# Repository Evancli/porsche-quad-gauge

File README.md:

# QUAD GAUGE FOR A PORSCHE 914
More info [here](https://evanli.com/quad-gauge-for-a-porsche-914/).

## Required Items
This gauge uses salvaged components from a Porsche 944 fuel gauge; the bezel, glass, and face plate. You can used the vintage gauges from the 944 or the corresponding gauges from your 914. It also required two new VDO gauges for voltage and oil pressure.

## Disassembly Tips
It's quite laborious to open these VDO gauges, even with the right tools. A prying spudger and flat implement are needed. Lots of care and attention to not mess up the sheet metal. Be very careful when you pry open the 944 fuel gauge. It's very easy damage the surface finish of the bezel. 

## Processes
The build uses 3D printed parts as well a laser cut and etched parts. 

## License
Shield: [![CC BY-SA 4.0][cc-by-sa-shield]][cc-by-sa]

This work is licensed under a
[Creative Commons Attribution-ShareAlike 4.0 International License][cc-by-sa].

[![CC BY-SA 4.0][cc-by-sa-image]][cc-by-sa]

[cc-by-sa]: http://creativecommons.org/licenses/by-sa/4.0/
[cc-by-sa-image]: https://licensebuttons.net/l/by-sa/4.0/88x31.png
[cc-by-sa-shield]: https://img.shields.io/badge/License-CC%20BY--SA%204.0-lightgrey.svg

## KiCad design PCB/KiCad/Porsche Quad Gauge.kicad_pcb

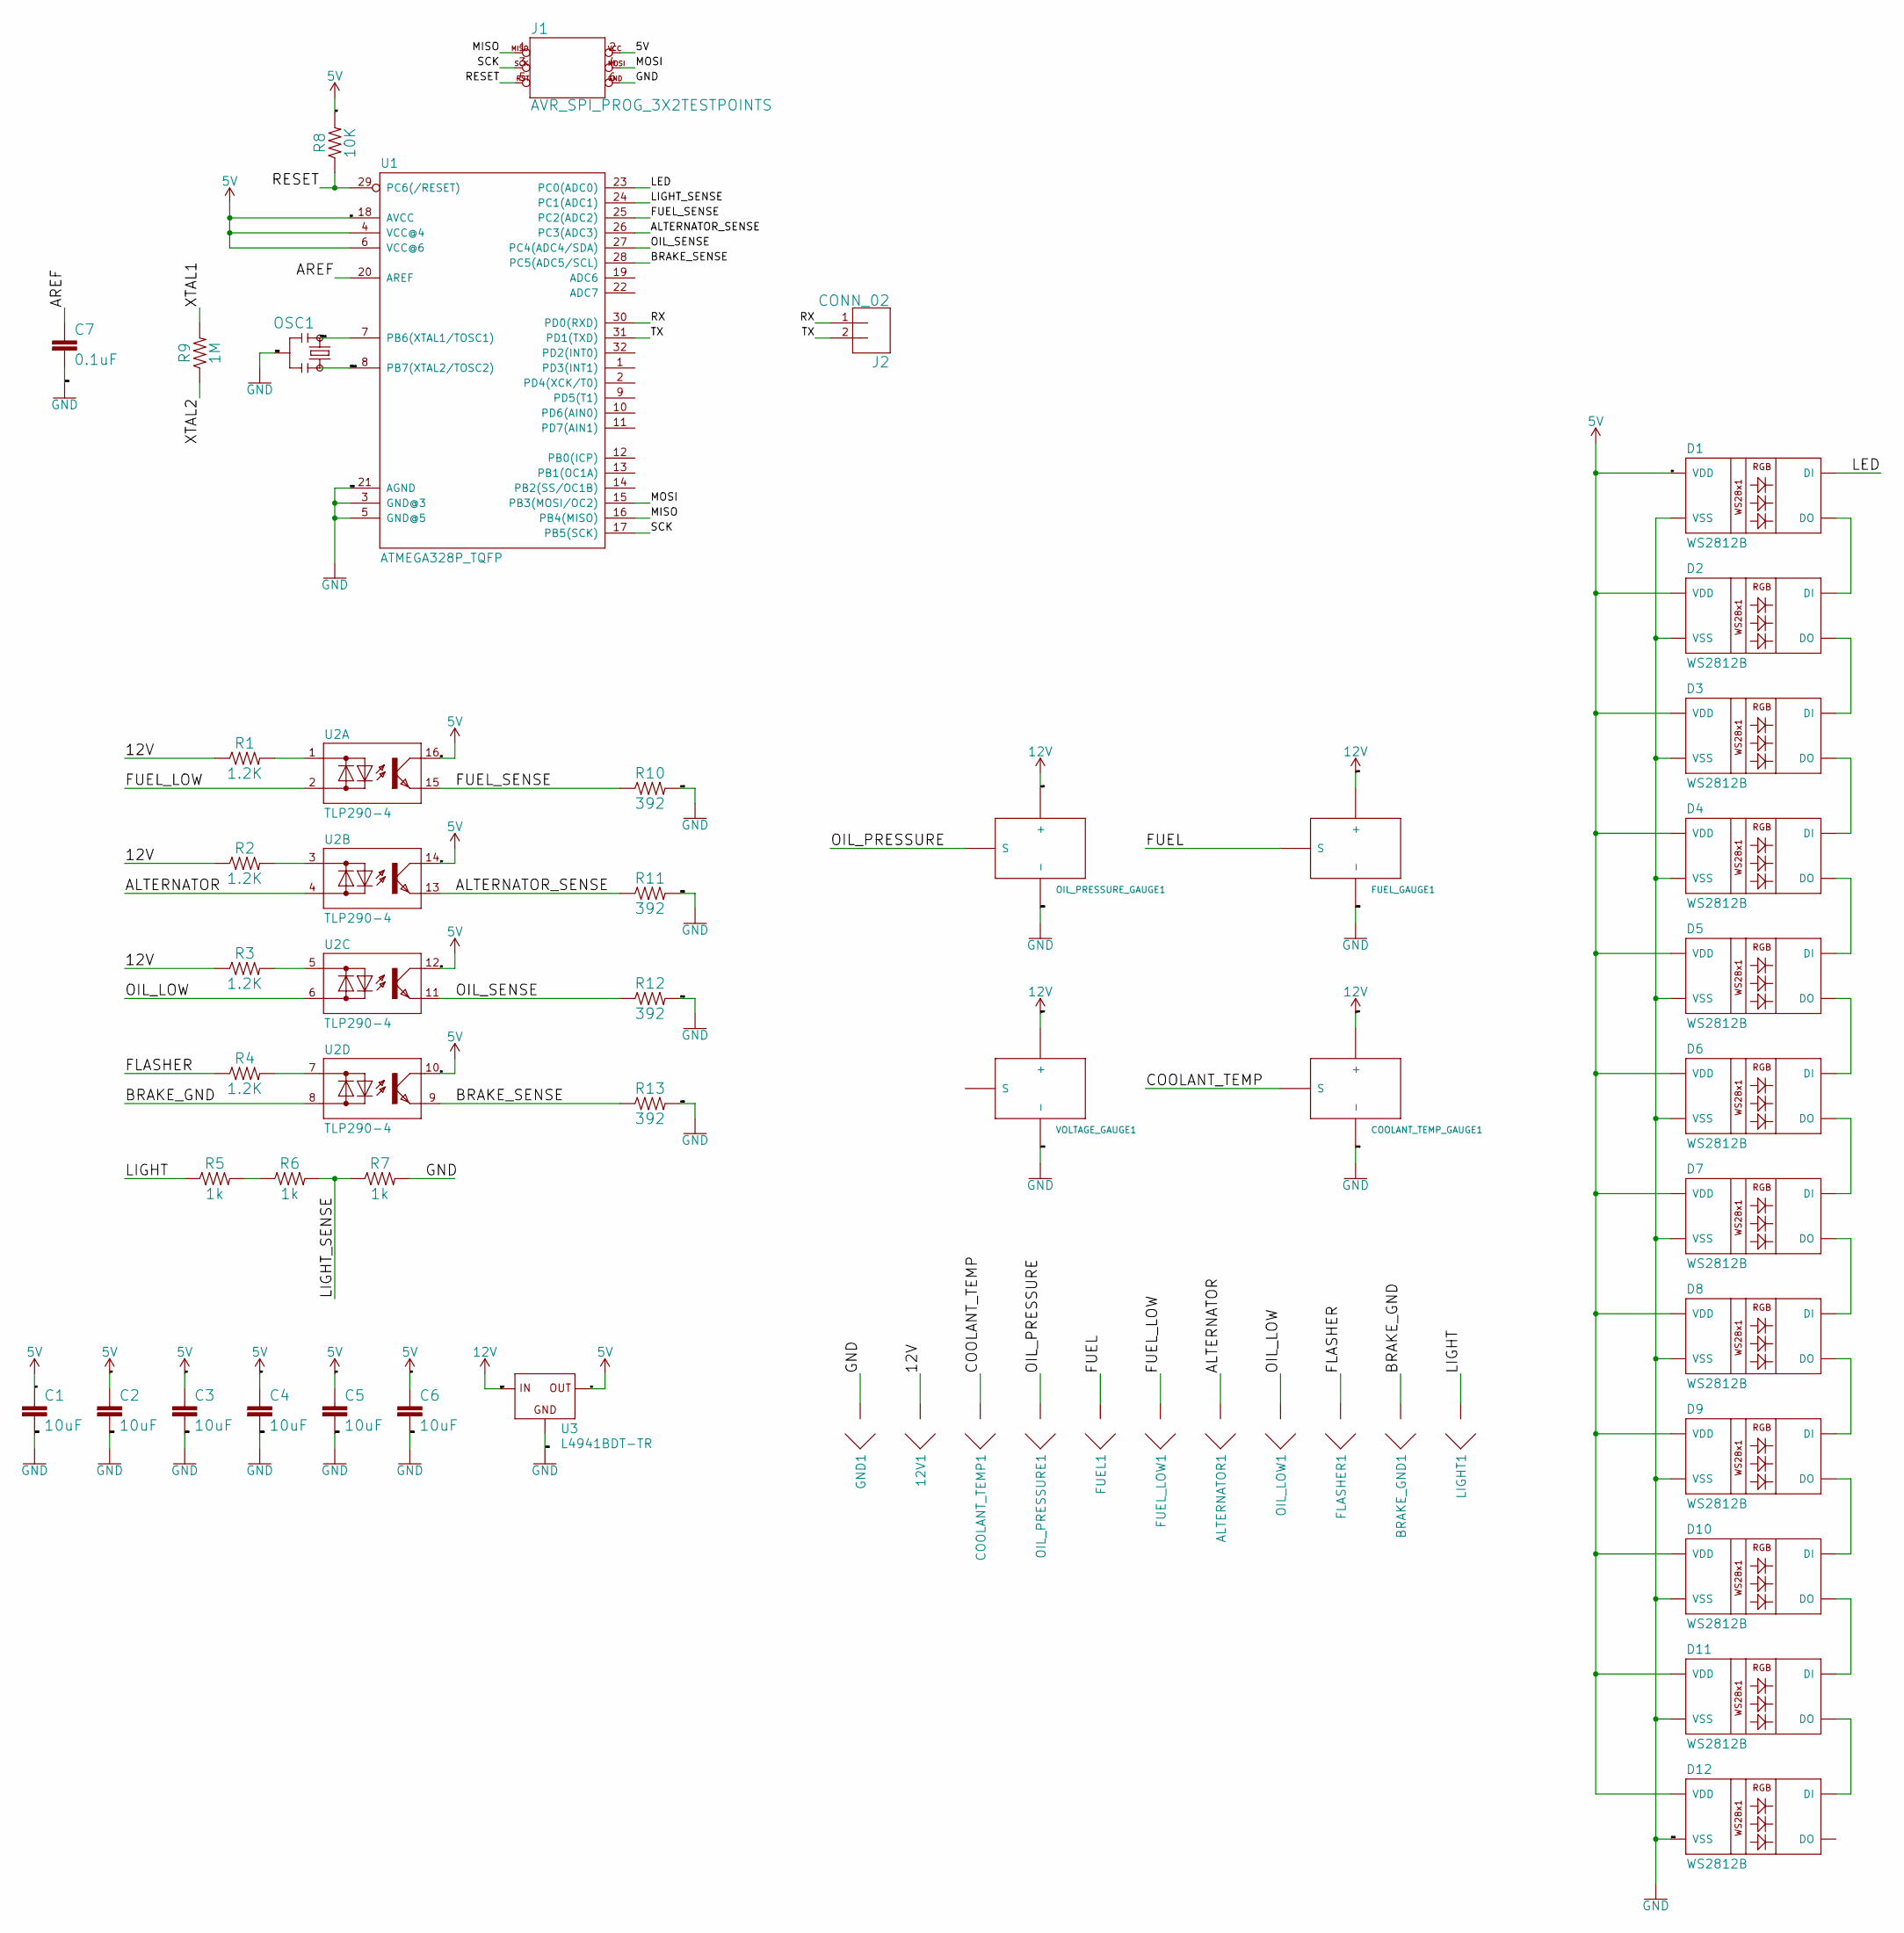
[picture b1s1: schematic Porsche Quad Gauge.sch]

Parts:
12V1: CONNECTOR_QC_TAB_0.25; CONNECTOR_QC_TAB-0.25
ALTERNATOR1: CONNECTOR_QC_TAB_0.25; CONNECTOR_QC_TAB-0.25
BRAKE_GND1: CONNECTOR_QC_TAB_0.25; CONNECTOR_QC_TAB-0.25
C1, C2, C3, C4, C5, C6: 10uF; 0805
C7: 0.1uF; 0805
COOLANT_TEMP1: CONNECTOR_QC_TAB_0.25; CONNECTOR_QC_TAB-0.25
COOLANT_TEMP_GAUGE1: VDO_OLD; VDO_GAUGE_SOCKET
D1, D2, D3, D4, D5, D6, D7, D8, D9, D10, D11, D12: WS2812B
FLASHER1: CONNECTOR_QC_TAB_0.25; CONNECTOR_QC_TAB-0.25
FUEL1: CONNECTOR_QC_TAB_0.25; CONNECTOR_QC_TAB-0.25
FUEL_GAUGE1: VDO_OLD; VDO_GAUGE_SOCKET
FUEL_LOW1: CONNECTOR_QC_TAB_0.25; CONNECTOR_QC_TAB-0.25
GND1: CONNECTOR_QC_TAB_0.25; CONNECTOR_QC_TAB-0.25
J1: AVR_SPI_PROG_3X2TESTPOINTS; 2X3_TEST_POINTS
J2: CONN_02; 1X02
LIGHT1: CONNECTOR_QC_TAB_0.25; CONNECTOR_QC_TAB-0.25
OIL_LOW1: CONNECTOR_QC_TAB_0.25; CONNECTOR_QC_TAB-0.25
OIL_PRESSURE1: CONNECTOR_QC_TAB_0.25; CONNECTOR_QC_TAB-0.25
OIL_PRESSURE_GAUGE1: VDO_NEW; VDO_NEW_GAUGE_SOCKET
OSC1: PRQC16.00SR1010V00L; 3-SMD
R1, R2, R3, R4: 1.2K; 0805
R5, R6, R7: 1k; 0805
R8: 10K; 0805
R9: 1M; 0805
R10, R11, R12, R13: 392; 0805
U1: ATMEGA328P_TQFP; TQFP32-08
U2: TLP290-4; SO16
U3: L4941BDT-TR; D-PAK_TO252AA
VOLTAGE_GAUGE1: VDO_NEW; VDO_NEW_GAUGE_SOCKET

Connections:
5V: C1.1, C2.1, C3.1, C4.1, C5.1, C6.1, D1.1 (VDD), D2.1 (VDD), D3.1 (VDD), D4.1 (VDD), D5.1 (VDD), D6.1 (VDD), D7.1 (VDD), D8.1 (VDD), D9.1 (VDD), D10.1 (VDD), D11.1 (VDD), D12.1 (VDD), J1.2, R8.2, U1.4 (VCC@4), U1.6 (VCC@6), U1.18 (AVCC), U2.10 (C), U2.12 (C), U2.14 (C), U2.16 (C), U3.3 (OUT)
12V: 12V1.S1, 12V1.S2, COOLANT_TEMP_GAUGE1.12V (+), FUEL_GAUGE1.12V (+), OIL_PRESSURE_GAUGE1.12V (+), R1.1, R2.1, R3.1, U3.1 (IN), VOLTAGE_GAUGE1.12V (+)
/ALTERNATOR: ALTERNATOR1.S1, ALTERNATOR1.S2, U2.4 (AC2)
/ALTERNATOR_SENSE: R11.1, U1.26 (PC3(ADC3)), U2.13 (E)
/AREF: C7.1, U1.20 (AREF)
/BRAKE_GND: BRAKE_GND1.S1, BRAKE_GND1.S2, U2.8 (AC2)
/BRAKE_SENSE: R13.1, U1.28 (PC5(ADC5/SCL)), U2.9 (E)
/COOLANT_TEMP: COOLANT_TEMP1.S1, COOLANT_TEMP1.S2, COOLANT_TEMP_GAUGE1.SIGNAL (S)
/FLASHER: FLASHER1.S1, FLASHER1.S2, R4.1
/FUEL: FUEL1.S1, FUEL1.S2, FUEL_GAUGE1.SIGNAL (S)
/FUEL_LOW: FUEL_LOW1.S1, FUEL_LOW1.S2, U2.2 (AC2)
/FUEL_SENSE: R10.1, U1.25 (PC2(ADC2)), U2.15 (E)
/LED: D1.4 (DI), U1.23 (PC0(ADC0))
/LIGHT: LIGHT1.S1, LIGHT1.S2, R5.1
/LIGHT_SENSE: R6.2, R7.1, U1.24 (PC1(ADC1))
/MISO: J1.1, U1.16 (PB4(MISO))
/MOSI: J1.4, U1.15 (PB3(MOSI/OC2))
/OIL_LOW: OIL_LOW1.S1, OIL_LOW1.S2, U2.6 (AC2)
/OIL_PRESSURE: OIL_PRESSURE1.S1, OIL_PRESSURE1.S2, OIL_PRESSURE_GAUGE1.SIGNAL (S)
/OIL_SENSE: R12.1, U1.27 (PC4(ADC4/SDA)), U2.11 (E)
/RESET: J1.5, R8.1, U1.29 (PC6(/RESET))
/RX: J2.1, U1.30 (PD0(RXD))
/SCK: J1.3, U1.17 (PB5(SCK))
/TX: J2.2, U1.31 (PD1(TXD))
/XTAL1: OSC1.XTAL1 (1), R9.2, U1.7 (PB6(XTAL1/TOSC1))
/XTAL2: OSC1.XTAL2 (3), R9.1, U1.8 (PB7(XTAL2/TOSC2))
GND: C1.2, C2.2, C3.2, C4.2, C5.2, C6.2, C7.2, COOLANT_TEMP_GAUGE1.GND (-), D1.3 (VSS), D2.3 (VSS), D3.3 (VSS), D4.3 (VSS), D5.3 (VSS), D6.3 (VSS), D7.3 (VSS), D8.3 (VSS), D9.3 (VSS), D10.3 (VSS), D11.3 (VSS), D12.3 (VSS), FUEL_GAUGE1.GND (-), GND1.S1, GND1.S2, J1.6, OIL_PRESSURE_GAUGE1.GND (-), OSC1.GND (2), R7.2, R10.2, R11.2, R12.2, R13.2, U1.3 (GND@3), U1.5 (GND@5), U1.21 (AGND), U3.2 (GND), VOLTAGE_GAUGE1.GND (-)
unnamed: D1.2 (DO), D2.4 (DI)
unnamed: D2.2 (DO), D3.4 (DI)
unnamed: D3.2 (DO), D4.4 (DI)
unnamed: D4.2 (DO), D5.4 (DI)
unnamed: D5.2 (DO), D6.4 (DI)
unnamed: D6.2 (DO), D7.4 (DI)
unnamed: D7.2 (DO), D8.4 (DI)
unnamed: D8.2 (DO), D9.4 (DI)
unnamed: D10.2 (DO), D11.4 (DI)
unnamed: D9.2 (DO), D10.4 (DI)
unnamed: D11.2 (DO), D12.4 (DI)
unnamed: R1.2, U2.1 (AC1)
unnamed: R2.2, U2.3 (AC1)
unnamed: R3.2, U2.5 (AC1)
unnamed: R4.2, U2.7 (AC1)
unnamed: R5.2, R6.1

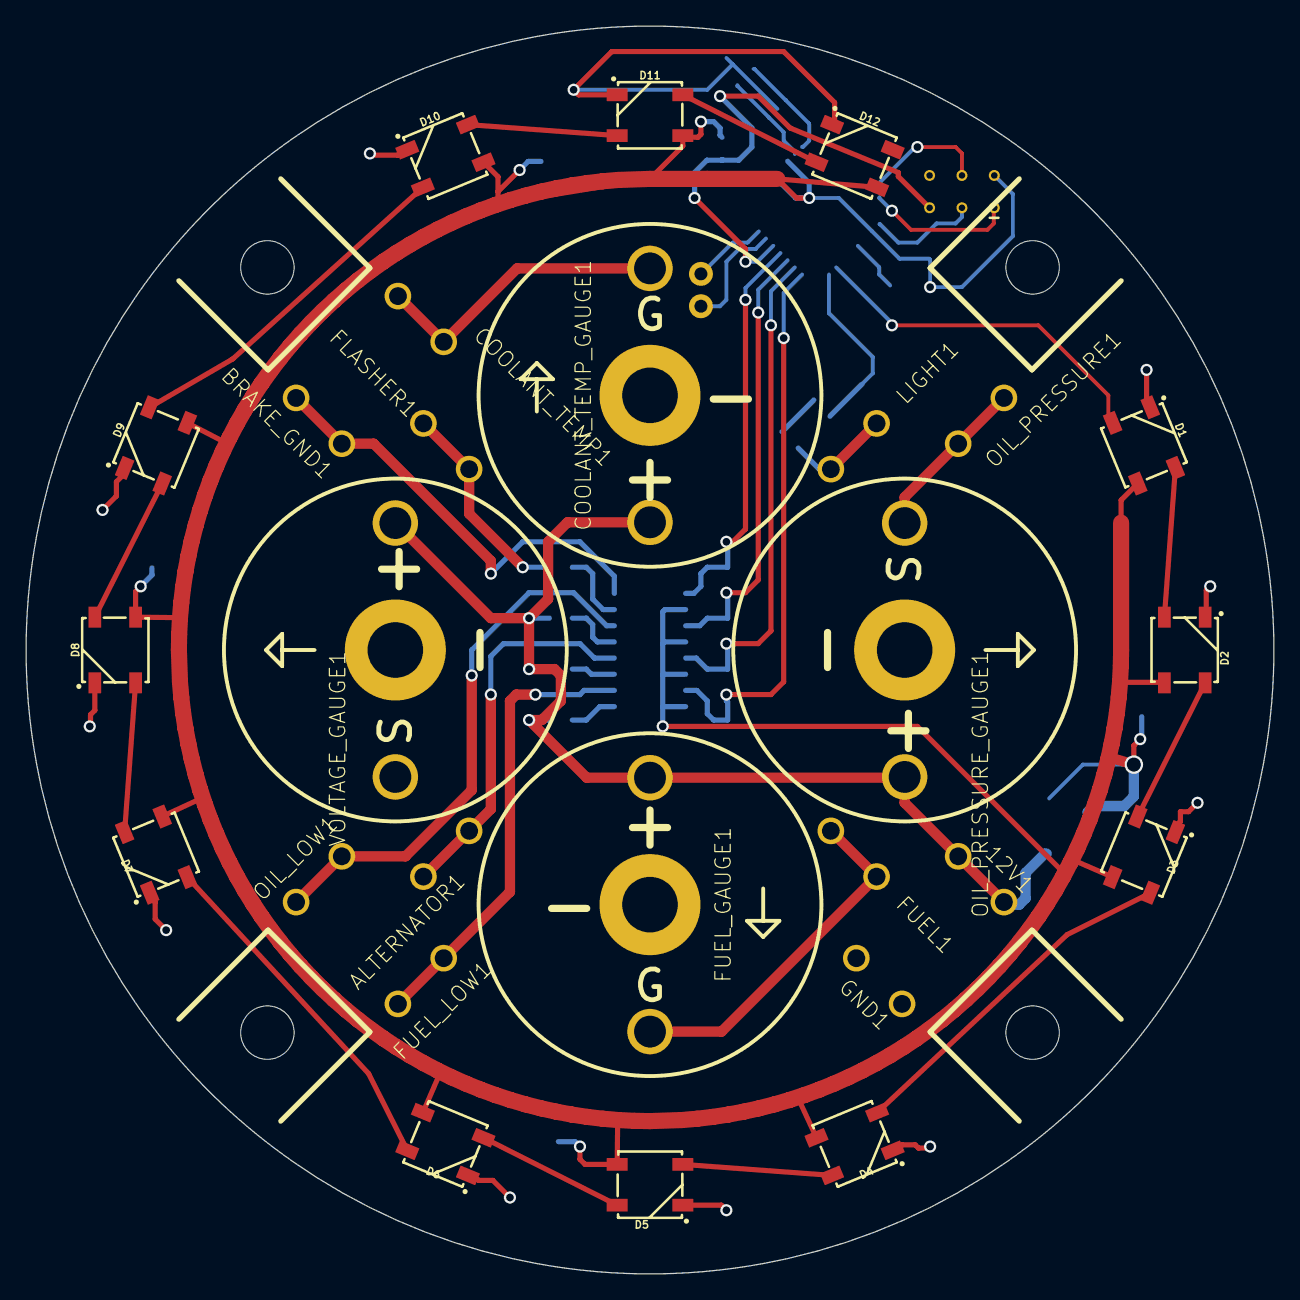
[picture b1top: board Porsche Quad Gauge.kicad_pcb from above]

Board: 2 copper layers, 98.0 x 98.0 mm, 57 parts (0 on the bottom side), 43 nets.

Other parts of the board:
@HOLE0, @HOLE1, @HOLE2, @HOLE3: (no value)

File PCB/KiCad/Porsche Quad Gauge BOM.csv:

"Source:","C:\Users\evanc\Dropbox\Projects\Porsche\Quad Gauge\PCB\KiCad\Porsche Quad Gauge.sch"
"Date:","12/14/2020 2:12:16 PM"
"Tool:","Eeschema (5.1.7)-1"
"Component Count:","53"
"Ref","Value","Footprint","Datasheet","Manufacturer","Vendor"
"12V1","CONNECTOR_QC_TAB_0.25","Porsche Quad Gauge:CONNECTOR_QC_TAB-0.25","","",""
"ALTERNATOR1","CONNECTOR_QC_TAB_0.25","Porsche Quad Gauge:CONNECTOR_QC_TAB-0.25","","",""
"BRAKE_GND1","CONNECTOR_QC_TAB_0.25","Porsche Quad Gauge:CONNECTOR_QC_TAB-0.25","","",""
"C1","10uF","Porsche Quad Gauge:0805","","",""
"C2","10uF","Porsche Quad Gauge:0805","","",""
"C3","10uF","Porsche Quad Gauge:0805","","",""
"C4","10uF","Porsche Quad Gauge:0805","","",""
"C5","10uF","Porsche Quad Gauge:0805","","",""
"C6","10uF","Porsche Quad Gauge:0805","","",""
"C7","0.1uF","Porsche Quad Gauge:0805","","",""
"COOLANT_TEMP1","CONNECTOR_QC_TAB_0.25","Porsche Quad Gauge:CONNECTOR_QC_TAB-0.25","","",""
"COOLANT_TEMP_GAUGE1","VDO_OLD","Porsche Quad Gauge:VDO_GAUGE_SOCKET","","",""
"D1","WS2812B","Porsche Quad Gauge:WS2812B","","",""
"D2","WS2812B","Porsche Quad Gauge:WS2812B","","",""
"D3","WS2812B","Porsche Quad Gauge:WS2812B","","",""
"D4","WS2812B","Porsche Quad Gauge:WS2812B","","",""
"D5","WS2812B","Porsche Quad Gauge:WS2812B","","",""
"D6","WS2812B","Porsche Quad Gauge:WS2812B","","",""
"D7","WS2812B","Porsche Quad Gauge:WS2812B","","",""
"D8","WS2812B","Porsche Quad Gauge:WS2812B","","",""
"D9","WS2812B","Porsche Quad Gauge:WS2812B","","",""
"D10","WS2812B","Porsche Quad Gauge:WS2812B","","",""
"D11","WS2812B","Porsche Quad Gauge:WS2812B","","",""
"D12","WS2812B","Porsche Quad Gauge:WS2812B","","",""
"FLASHER1","CONNECTOR_QC_TAB_0.25","Porsche Quad Gauge:CONNECTOR_QC_TAB-0.25","","",""
"FUEL1","CONNECTOR_QC_TAB_0.25","Porsche Quad Gauge:CONNECTOR_QC_TAB-0.25","","",""
"FUEL_GAUGE1","VDO_OLD","Porsche Quad Gauge:VDO_GAUGE_SOCKET","","",""
"FUEL_LOW1","CONNECTOR_QC_TAB_0.25","Porsche Quad Gauge:CONNECTOR_QC_TAB-0.25","","",""
"GND1","CONNECTOR_QC_TAB_0.25","Porsche Quad Gauge:CONNECTOR_QC_TAB-0.25","","",""
"J1","AVR_SPI_PROG_3X2TESTPOINTS","Porsche Quad Gauge:2X3_TEST_POINTS","","",""
"J2","CONN_02","Porsche Quad Gauge:1X02","","",""
"LIGHT1","CONNECTOR_QC_TAB_0.25","Porsche Quad Gauge:CONNECTOR_QC_TAB-0.25","","",""
"OIL_LOW1","CONNECTOR_QC_TAB_0.25","Porsche Quad Gauge:CONNECTOR_QC_TAB-0.25","","",""
"OIL_PRESSURE1","CONNECTOR_QC_TAB_0.25","Porsche Quad Gauge:CONNECTOR_QC_TAB-0.25","","",""
"OIL_PRESSURE_GAUGE1","VDO_NEW","Porsche Quad Gauge:VDO_NEW_GAUGE_SOCKET","","",""
"OSC1","PRQC16.00SR1010V00L","Porsche Quad Gauge:3-SMD","","",""
"R1","1.2K","Porsche Quad Gauge:0805","","",""
"R2","1.2K","Porsche Quad Gauge:0805","","",""
"R3","1.2K","Porsche Quad Gauge:0805","","",""
"R4","1.2K","Porsche Quad Gauge:0805","","",""
"R5","1k","Porsche Quad Gauge:0805","","",""
"R6","1k","Porsche Quad Gauge:0805","","",""
"R7","1k","Porsche Quad Gauge:0805","","",""
"R8","10K","Porsche Quad Gauge:0805","","",""
"R9","1M","Porsche Quad Gauge:0805","","",""
"R10","392","Porsche Quad Gauge:0805","","",""
"R11","392","Porsche Quad Gauge:0805","","",""
"R12","392","Porsche Quad Gauge:0805","","",""
"R13","392","Porsche Quad Gauge:0805","","",""
"U1","ATMEGA328P_TQFP","Porsche Quad Gauge:TQFP32-08","","",""
"U2","TLP290-4","Porsche Quad Gauge:SO16","","",""
"U3","L4941BDT-TR","Porsche Quad Gauge:D-PAK_TO252AA","","",""
"VOLTAGE_GAUGE1","VDO_NEW","Porsche Quad Gauge:VDO_NEW_GAUGE_SOCKET","","",""

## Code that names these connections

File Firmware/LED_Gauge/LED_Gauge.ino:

#include <Arduino.h>

#include <Adafruit_NeoPixel.h>

#ifdef __AVR__
  #include <avr/power.h>
#endif

#define LED_PIN 14
#define LIGHT_SENSE A1
#define FUEL_SENSE 16
#define ALTERNATOR_SENSE 17
#define OIL_SENSE 18
#define BRAKE_SENSE 19

#define MAX_BRIGHTNESS 128

#define LED_COUNT 12

// Ref: https://learn.adafruit.com/adafruit-neopixel-uberguide/arduino-library
Adafruit_NeoPixel leds = Adafruit_NeoPixel(LED_COUNT, LED_PIN, NEO_RGBW + NEO_KHZ800);

int lightSenseValue = 0;
int fuelSenseValue = 0;
int alternatorSenseValue = 0;
int oilSenseValue = 0;
int brakeSenseValue = 0;

int brightnessValue = 0;

/// RGBW seems to be GRBW
uint32_t fuelColor = leds.Color(128, 255, 0, 0); // leds.Color(255, 128, 0, 0);
uint32_t alternatorColor = leds.Color(0, 255, 0, 0);
uint32_t oilColor = leds.Color(255, 0, 0, 0);
uint32_t brakeColor = leds.Color(0, 255, 0, 0);

void setup() {

  pinMode(FUEL_SENSE, INPUT);
  pinMode(ALTERNATOR_SENSE, INPUT);
  pinMode(OIL_SENSE, INPUT);
  pinMode(BRAKE_SENSE, INPUT);

  leds.setBrightness(MAX_BRIGHTNESS);

  leds.begin();
  leds.show();
}

void loop() {

  lightSenseValue = analogRead(LIGHT_SENSE);
  fuelSenseValue = digitalRead(FUEL_SENSE);
  alternatorSenseValue = digitalRead(ALTERNATOR_SENSE);
  oilSenseValue = digitalRead(OIL_SENSE);
  brakeSenseValue = digitalRead(BRAKE_SENSE);



  brightnessValue = map(lightSenseValue, 0, 1023, 0, 128);



  for (int i = 0; i < LED_COUNT; i++) {
    leds.setPixelColor(i, leds.Color(0, 0, 0, brightnessValue));

    if (i >= 0 && i < 3 && oilSenseValue) {
      leds.setPixelColor(i, oilColor );
    }

    if (i >= 3  && i < 6 && fuelSenseValue) {
      leds.setPixelColor(i, fuelColor );
    }

    if (i >= 6 && i < 9 && alternatorSenseValue) {
      leds.setPixelColor(i, alternatorColor);
    }

    if (i >= 9 && i < 12 && brakeSenseValue) {
      leds.setPixelColor(i, brakeColor);
    }
  }


//  for (int i = 0; i < 24; i++) {
//    if (i < brightness) {
//      leds.setPixelColor(i, leds.Color(255, 0, 0));
//    } else {
//      leds.setPixelColor(i, leds.Color(0, 0, 0));
//    }
//  }

  leds.show();
  delay(50);
}

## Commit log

2020-12-14 Technical information packet.
2020-12-15 Update README.md
    Added more information.

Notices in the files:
parts and their libraries:
SparkFun-Resistors: Licensing: Creative Commons ShareAlike 4.0 International - https://creativecommons.org/licenses/by-sa/4.0
